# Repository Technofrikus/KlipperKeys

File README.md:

# Klipper Keys

__For pictures etc see: https://www.printables.com/model/539404-klipper-keys-keyboard-for-3030-and-2020-profiles__

This “keyboard” with 5 keys gets conneted directly to the GPIOs of the RasbperryPi. This way no MCU or anything fancy is needed. The case is tested on a vCore 3.1 400mm with 3030 profiles. Not sure about clearance on other printers. But electrically should also work for Vorons etc.

For me light switching during printing is not super reliable. Not sure why. Everything else works great.

The PCB is OpenSource and all files, including production files, can be found here:

https://github.com/Technofrikus/KlipperKeys

You need:

## BOM:

### Printing
1x Case
1x Baseplate (choose which profile size you need)
1x PCB

### Cable
6-wire cable in your needed length
both ends crimped with Dupont connectors (standard 2.54mm pitch)

### Hardware
1x 6-pin-header
4x M3 threaded insert (5,7mm length or shorter work)
4x M3x10 screw

#### For 2020 profile
2x M3x8/10
2x hammer nut
Can also use bigger screws (not longer), just have to increase the size of the hole a little with a knife.

#### For 3030 profile
2x M5/6x12
2x hammer nut with the same thread size
5x MX-compatible switches and keycaps
Try these printable relegendable keycaps I used with some tips for printing: https://www.thingiverse.com/make:912979

### Connecting

The Pins are named on the PCB. Also check the picture for the marked pins. Reference: https://pinout.xyz
Configuration

Then add these settings to your macro-file. I have a user-macro-cfg which I included from printer.cfg to have these things separate. But you can also put it directly in the printer.cfg
These gcodes are custom to my setup (lights) and RatOS (unload_filament). Please change these to your liking and printer setup.
```
[gcode_button button_light]
pin: ~rpi:gpio17
press_gcode: CASE_LIGHTS_TOGGLE

[gcode_button button_load]
pin: ~rpi:gpio9
press_gcode: LOAD_FILAMENT

[gcode_button button_unload]
pin: ~rpi:gpio10
press_gcode: UNLOAD_FILAMENT

[gcode_button button_PLATemp]
pin: ~rpi:gpio22
press_gcode:
 SET_HEATER_TEMPERATURE HEATER=extruder TARGET=200
 SET_HEATER_TEMPERATURE HEATER=heater_bed TARGET=60

[gcode_button button_cooldown]
pin: ~rpi:gpio27
press_gcode:
 TURN_OFF_HEATERS
```

If you want to use a Button as an Emergency-Stop, use this code:
```
[gcode_button ESTOP_BUTTON]
pin: ...
press_gcode:  
   {action_emergency_stop("Impending Doom Averted!")}
```
I have not tested this, but ThaoChan provided it and it works for him. Thanks again Thao for your help with the Config! Check it out here: https://www.reddit.com/r/klippers/comments/ssj67j/comment/ju6ld9p/?utm_source=reddit&utm_medium=web2x&context=3

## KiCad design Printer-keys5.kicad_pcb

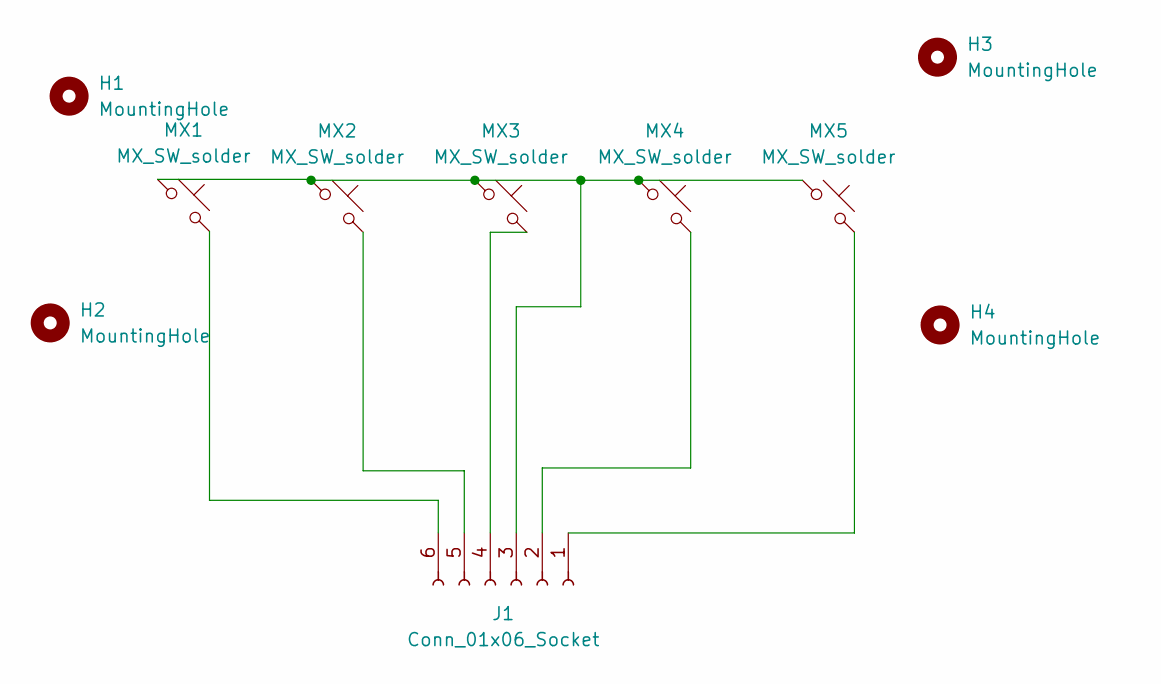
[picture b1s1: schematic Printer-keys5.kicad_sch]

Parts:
H1, H2, H3, H4: MountingHole; MountingHole_3.2mm_M3
J1: Conn_01x06_Socket; PinHeader_1x06_P2.54mm_Vertical
MX1, MX2, MX3, MX4, MX5: MX_SW_solder; SW_MX_1u

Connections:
unnamed: J1.1, MX5.2
unnamed: J1.2, MX4.2
unnamed: J1.3, MX1.1, MX2.1, MX3.1, MX4.1, MX5.1
unnamed: J1.4, MX3.2
unnamed: J1.5, MX2.2
unnamed: J1.6, MX1.2

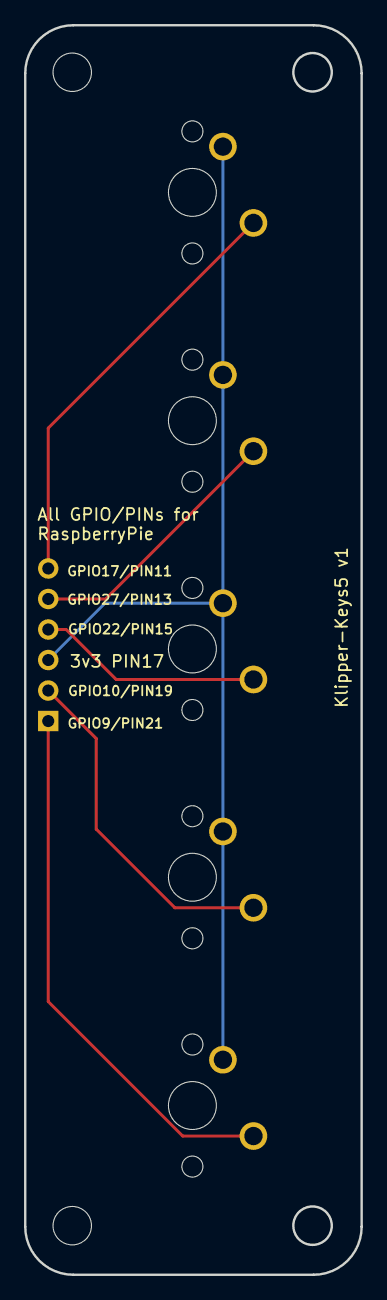
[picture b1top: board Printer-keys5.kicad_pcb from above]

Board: 2 copper layers, 28.0 x 104.0 mm, 10 parts (1 on the bottom side), 6 nets.

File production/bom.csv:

Designator,Footprint,Quantity,Value,LCSC Part #
"H1, H2, H3, H4",MountingHole_3.2mm_M3,4,MountingHole,
J1,PinHeader_1x06_P2.54mm_Vertical,1,Conn_01x06_Socket,
"MX1, MX2, MX3, MX4, MX5",SW_MX_1u,5,MX_SW_solder,

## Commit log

2023-07-21 initial upload
2023-07-23 small kinks ironed out after testprint
2023-07-30 Updated case with more options and small improvements
2023-07-30 Rename
2023-07-31 Updated config so it works
